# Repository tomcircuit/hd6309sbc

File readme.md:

# Hitachi HD6309 Singleboard Computer - V1
 
The HD6309 SBC is a retroputing distraction, born to provide an opportunity to try my hand at assembly language for the 6809 - which many have billed as "the most advanced 8-bit processor" ever. The Hitachi 6309 variant is **even more advanced**, with significant extensions from the base Motorola 6809 ISA. 

There are many 8bit SBC (singleboard computers) in the wild, each developed according to the designers' vision. Some go for strict hardware implementation using only vintage components, while others take advantage of modern FPGAs and encapsulate nearly everything into a single device. For this particular SBC, I went for a blend of *old skool* and *all mod cons*. For example, the primary interface is ASCII serial, but the physical layer is implemented as a FDTI USB
bridge chip, as I loathe having to use RS232 adapters. Similarly, I included a SPI-mode SD card interface, rather than the purist approach of an actual floppy drive. I use a CPLD for all the glue logic for ease of reconfiguring address mapping and supporting built-in control registers. Fortunately, it all can be powered from the USB port (<250mA at last measurement).

## HD6309 SBC V1 Hardware

Version 1 of the SBC hardware has the following features:

 - 3 MHz Hitachi HD63C09 microprocessor 
 - 64KB RAM (2x 32KB SRAM)
 - 32KB EPROM (27C256) 
 - Parallel Interface & Timers (Zilog Z8536 CIO)
 - Dual Serial Channels (Zilog Z85C30 SCC)   
 - USB slave (FTDI FT230XS) connected to SCC Ch. A
 - Realtime Clock (Epson RTC7301)  w/ CR2032 backup 
 - SPI-mode micro-SD memory card (CPLD hardware SPI)
 - RESET pushbutton
 - USER pushbutton (read via CPLD)
 - 2 USER LED's (control via CPLD)
 - USB RX/TX Activity LED
 - SD card Activity LED
 - Expansion Connector (bus signals)

Hardware wise, the short-term goal is met: it all functions and works as intended. Several people have built this SBC from the files I provided, and the feedback has been helpful. 

Future hardware features to consider would be elimination of the CIO chip (seldom used), a better SCC (faster baudrate) and more memory and associated MMU. To do any/all of these, a bigger CPLD is required, as the MAX7128 is nearly fully used. 

> UPDATE: The Epson RTC is nearly unobtainable now, so I've made a small PCB to hold an I2C RTC that plugs into the Epson RTC socket. The CPLD has been changed, accordingly, to add a bitbanged I2C port.

## HD6309 SBCV1  Firmware

It seems to be an axiom that every SBC has a ROM resident monitor. Over the years, I've used a number of different monitors on this SBC. For my own use I've ported the (excellent) Dave Dunfield MON09 to this SBC but, sadly, this is not open source and cannot be redistributed. What I include in this repository is a ported version of "WOZMON", the Apple 1 monitor. It's enough to examine and modify memory, and load Intel hex and Motorola S-record files.

Assembly language is fun and all, but having a ROM-resident BASIC interpreter is even better. Grant Searle to the rescue,
who has dissected and commented 6809 MICROSOFT BASIC, which I easily adapted to this SBC.

The SBC has 32K of ROM (either a 27C256 or a 27C512 will work) that is accessed as two ~16K banks. The **CONFIG** jumper (JP4) selects the active ROM bank at RESET. Therefore, this jumper can be used to select between booting into MSBASIC or into WOZMON. 

Future software goals would be to port some sort of operating system, such as NitrOS-9 operating system (level I). Here I am completely a noob; I've never used OS-9 at all, but it seems like a nice OS. I think that more memory would really be required to support this.

There is a 'user manual' in the root of this repository that provides more information on the SBC.

The most up-to-date information on the SBC can be found on the Hackaday project page: https://hackaday.io/project/345-hd6309-singleboard-computer

This work is licensed under the Creative Commons Attribution-ShareAlike 4.0 International License. 
To view a copy of this license, visit http://creativecommons.org/licenses/by-sa/4.0/.

HD6309 Singleboard Computer (SBC)
Tom LeMense
12/7/2020

tomcircuit@gmail.com
@TomLeMense

<!--stackedit_data:
eyJoaXN0b3J5IjpbMTIxNDkzNTY1MCwyMTI2NjI3MTI3LDE3OT
U5OTEwNzUsNjMzMjQzNzc0LDEyNjEyNjI1NjFdfQ==
-->

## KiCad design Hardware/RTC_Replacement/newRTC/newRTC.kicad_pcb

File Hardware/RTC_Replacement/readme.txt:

This set of design files implements a replacement for the Epson RTC7301DG realtime clock

Design tool is KiCAD v5.1.4

This is a hack to replace the 4-bit parallel Epson RTC7301 RTC with an I2C Maxim DS3232M RTC.
As such, it's not a 100% drop in replacement, and is intended ONLY for use with the HD6309 SBC!

PCB was designed with hand-soldering in mind, and uses the hand-solder KiCAD PCB footprints.
I favor 0805 passives, in an attempt to enable easy hand-assembly.

My PCB were fabricated by OSHpark https://oshpark.com/ 

More up-to-date information on the SBC can be found on the Hackaday project page:
https://hackaday.io/project/345-hd6309-singleboard-computer

This work is licensed under the Creative Commons Attribution-ShareAlike 4.0 International License. 
To view a copy of this license, visit http://creativecommons.org/licenses/by-sa/4.0/.

HD6309 Singleboard Computer (SBC)
Tom LeMense
1/28/2020

tomcircuit@gmail.com
@TomLeMense

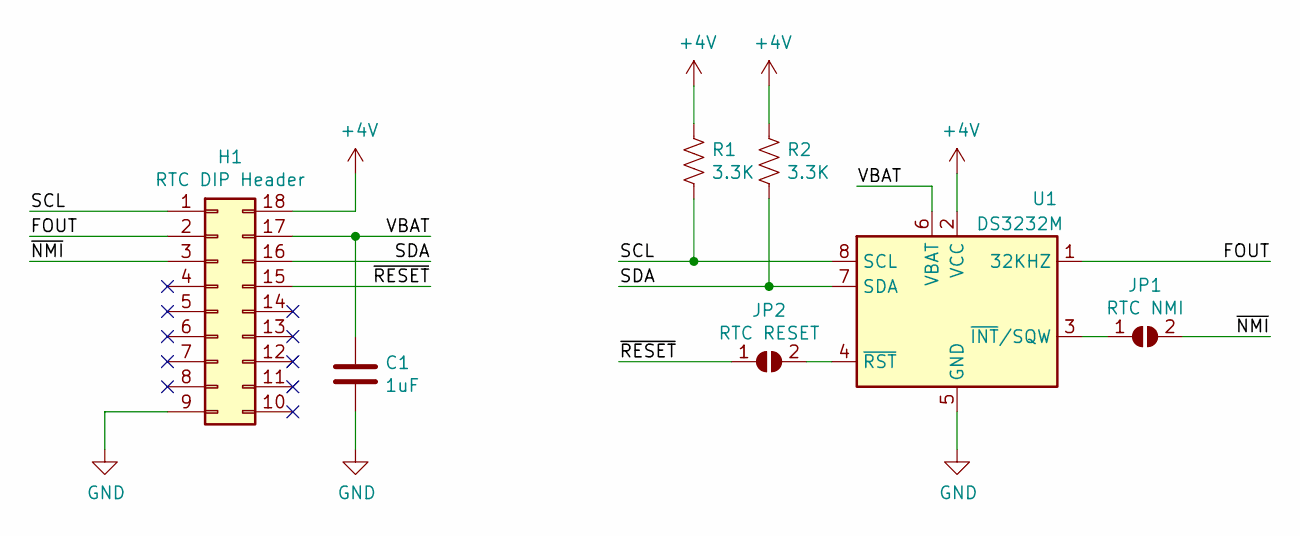
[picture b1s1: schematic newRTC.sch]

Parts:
C1: 1uF; C_0603_HandSoldering
H1: RTC DIP Header; RTC-DIP-Header
JP1: RTC NMI; GS2
JP2: RTC RESET; GS2
R1, R2: 3.3K; R_0603_HandSoldering
U1: DS3232M; SOIC-8_3.9x4.9mm_Pitch1.27mm

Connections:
+4V: H1.18, R1.1, R2.1, U1.2 (VCC)
/FOUT: H1.2, U1.1 (32KHZ)
/SCL: H1.1, R1.2, U1.8 (SCL)
/SDA: H1.16, R2.2, U1.7 (SDA)
/VBAT: C1.1, H1.17, U1.6 (VBAT)
/~NMI: H1.3, JP1.2 (B)
/~RESET: H1.15, JP2.1 (A)
GND: C1.2, H1.9, U1.5 (GND)
unnamed: JP1.1 (A), U1.3 (~INT~/SQW)
unnamed: JP2.2 (B), U1.4 (~RST)

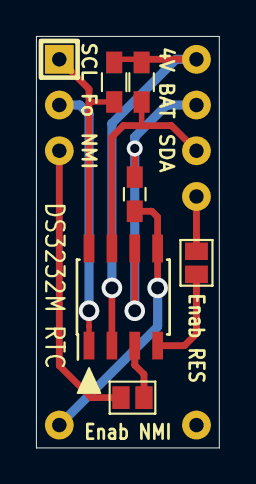
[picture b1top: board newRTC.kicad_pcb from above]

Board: 2 copper layers, 10.2 x 22.9 mm, 7 parts (0 on the bottom side), 10 nets.

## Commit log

2014-03-13 Initial commit
    Hardware folders; CPLD, PCB, Schematic. Software folder; Test
2014-03-13 Correction to readme.txt
2014-03-22 CPLD version 1.2
    Moved IOPAGE from $02xx to $C0xx
    Reordering of SYSCONF and INOUTP control bits
    Renamed SDPORT to SDDATA
    New SDDATA update mechanism (SR FF)
    Corrected SPI bit shift order (MSB shifts first)
    Implemented two SPI clock rates (6 MHz; 460kHz)
2014-03-22 Bumped version #
2014-03-22 SDtest update; Montest addition
    SDtest adapted for new IOPAGE value, changes to hardware SPI port with
    CPLD version 1.2
    Montest is a short test of the banked RAM feature; moves the monitor to
    high RAM, turns off ROMSEL
2014-03-23 sorted out SDcard test program
    SD init and restart issue solved. WARNING: test program trashes the last
    byte of LBA block 00123456.
2014-04-23 ROM BASIC initial release
    A nice adaptation of Microsoft CoCo Extended BASIC with the heavy
    lifting done by Grant Searle. Working as a standalone ROM on the hd6309
    SBC.
2014-05-01 SCC channel B UART test
    Test to send characters via SCC channels A and B
2014-05-01 Added FPGA mezzanine card PCB and SCH
    PCB gerber and database for the FPGA mezzanine shifter card (5V to 3.3V)
    for use with Altera DE1 FPGA eval board in developing the VGA+Audio+PS/2
    FPGA extension.
2014-05-25 CPLD Version 1.3
    Move IO to $E000-$E1FF, add version register, split ROM around the IO
    page, ROM "writethru" into RAM, two ROM selects (ROMSEL and ROMSEH).
2014-05-25 ROM BASIC updated for CPLD V1.3
    With new CPLD comes new ROM BASIC release - no real changes other than
    to juggle around the BASIC interpreter code to fit around the IO area
    from $E000-$E1FF.
2020-01-28 CPLD 1.3 cleanup / CPLD 1.4
    cleanup CPLD 1.3 files, include CPLD output files, add CPLD 1.4 files, update readme.txt throughout.
2020-01-28 Added RTC7301 replacement board
    KiCAD project and output files for RTC7301DG replacement board
2020-01-29 Monitor / RTC for V1.4 CPLD
    in-process files for I2C and adaption to V1.4 CPLD for Monitor
2020-01-31 grinding away at I2C driver
2020-02-17 Update MON309_1V4.ASM
    still grinding away at soft I2C functions
2020-02-18 Update MON309_1V4.ASM
    implemented all I2C functions.
    Untested.
    Need to add "I2C_Initialize" which toggles SCL untl SDA goes high, per the DS3232 datasheet
2020-03-20 work continues on a new 1.4 monitor ROM
    not quite ready to integrate mondeb.
    need to clean up SD card functions
2020-03-22 floating point integration
    cleaned up the floating point binary image (was too long!)
    included into ASM code
2020-03-23 adjusted structure to be more modular
2020-03-26 updated SPI and SD code
    reconciled SD code vs. Elm-Chan code.
    ready for build and test
2020-04-30 Monitor 1.41
    Monitor 1.41 completed. RTC and SD support tested. Wozmon tested. NoICE integration complete.
2020-05-01 CPLD v1.41 experiment
    Mapped SDdata to a second peripheral register ($E070) from which a read will force an SPI transaction. This is to see if the 6309 TFM instruction can be used for fast data transfer from SD card to me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
2020-05-11 updated test code for CPLD 1.41, I2C master
    Updated SDTEST, WOZ, and RTC test files. The attempt at supporting the TFM command didn't work very well - the SPI transaction is longer than the 2 CPU cycles. Attempt at inserting wait states worked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
    Attempt at an I2C master for inclusion in Hardware 2.0 / CPLD "1v5". Mostly to see how many macrocells required to implement...
2020-05-11 fixed VHDL
2020-12-07 migrate README to MD
    new format for readme file
2020-12-07 readme.md updated from https://stackedit.io/
